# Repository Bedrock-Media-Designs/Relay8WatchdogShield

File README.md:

# Relay 8 Watchdog Shield for Relay Shield Carrier
Copyright 2019 Bedrock Media Productions Pty Ltd www.bedrockmediaproductions.com.au

EtherTen Shield for the SuperHouse Automation Relay Shield Carrier Board

Features:

watchdog Timer, Routed into Digital Pin 8
I2C Header for easy connection to the Relay Shield Carrier Board
More information:

Relay Carrier Shield <https://www.superhouse.tv/product/relay-shield-carrier-x4/>

Relay8 Watchdog Shield <https://bedrockmediaproductions.com.au/product/r8wds/>

 ## INSTALLATION
The design is saved as an EAGLE project. EAGLE PCB design software is available from www.cadsoftusa.com free for non-commercial use. To use this project download it and place the directory containing these files into the "eagle" directory on your computer. Then open EAGLE and navigate to the project.

 ## CREDITS
Designed by: 

Jonathan Oxer jon@oxer.com.au (Protoshort Layout for EtherTen)

James Kennewell james@bedrockmediaproductions.com.au (circuit design)

## DISTRIBUTION
The specific terms of distribution of this project are governed by the license referenced below.

## LICENSE
Licensed under the TAPR Open Hardware License (www.tapr.org/OHL). The "license" folder within this repository also contains a copy of this license in plain text format.

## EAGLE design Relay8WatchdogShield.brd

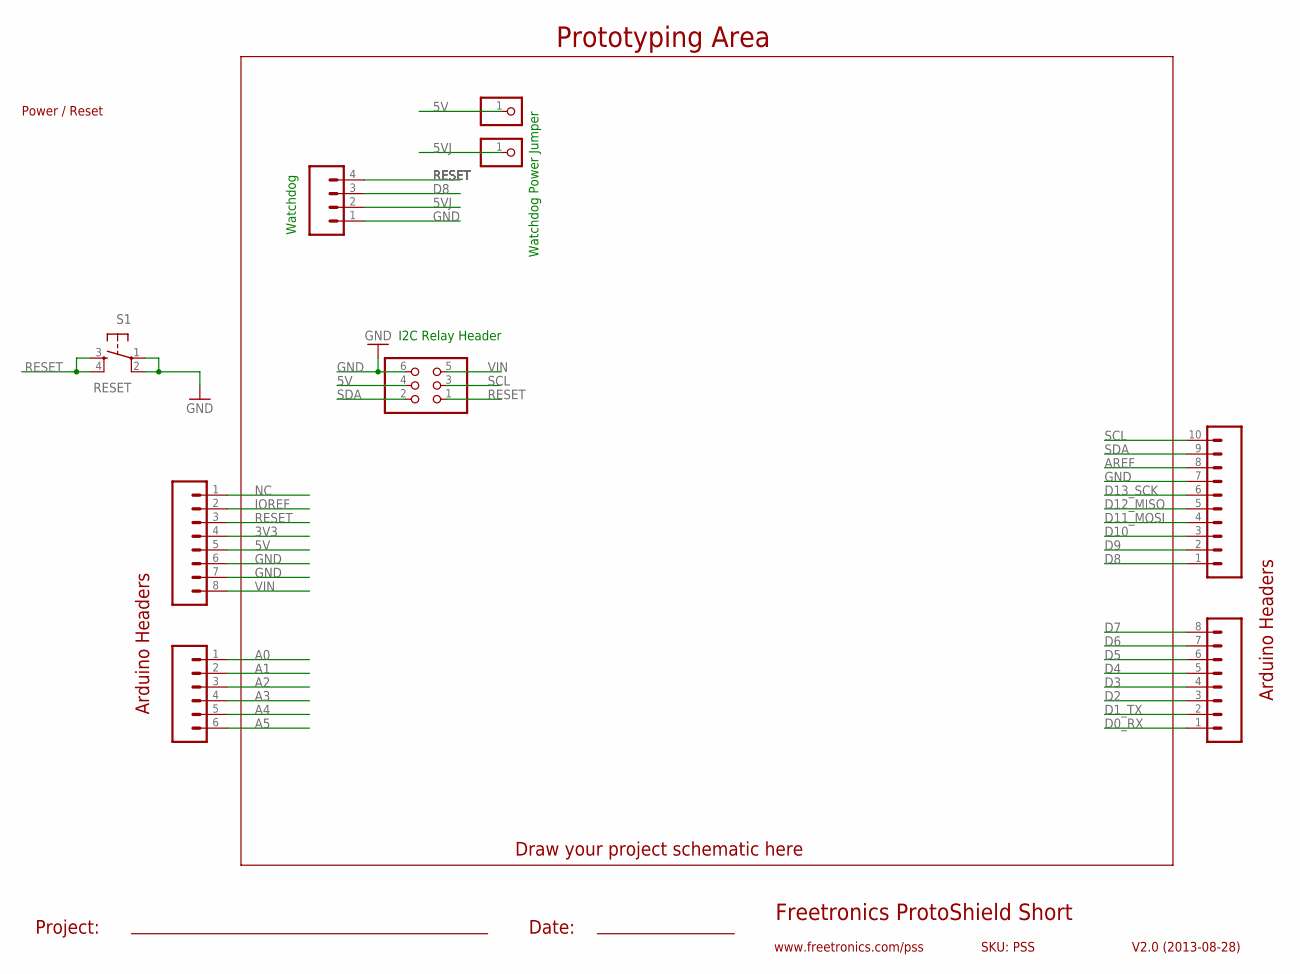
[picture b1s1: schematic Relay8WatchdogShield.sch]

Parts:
J1: Digital_0_7; 1X08
J2: Analog; 1X06
J3: Digital_8_13; 1X10
JP1, JP2: PINHD-1X1; 1X01
JP3: FREETRONICS-MASTER-V1_M04PTH; FREETRONICS-MASTER-V1_1X04
JP4: PINHD-2X3; 2X03
POWER: Power; 1X08
S1: RESET; TACTILE-PTH

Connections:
3V3: POWER.4
5V: JP1.1, JP4.4, POWER.5
5VJ: JP2.1, JP3.2
A0: J2.1
A1: J2.2
A2: J2.3
A3: J2.4
A4: J2.5
A5: J2.6
AREF: J3.8
D0_RX: J1.1
D1_TX: J1.2
D2: J1.3
D3: J1.4
D4: J1.5
D5: J1.6
D6: J1.7
D7: J1.8
D8: J3.1, JP3.3
D9: J3.2
D10: J3.3
D11_MOSI: J3.4
D12_MISO: J3.5
D13_SCK: J3.6
GND: J3.7, JP3.1, JP4.6, POWER.6, POWER.7, S1.1, S1.2
IOREF: POWER.2
NC: POWER.1
RESET: JP3.4, JP4.1, POWER.3, S1.3, S1.4
SCL: J3.10, JP4.3
SDA: J3.9, JP4.2
VIN: JP4.5, POWER.8

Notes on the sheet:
Freetronics ProtoShield Short
V2.0 (2013-08-28)
www.freetronics.com/pss
SKU: PSS
Prototyping Area
Arduino Headers
Power / Reset
Project:
Date:
Draw your project schematic here
Watchdog
I2C Relay Header
Watchdog Power Jumper

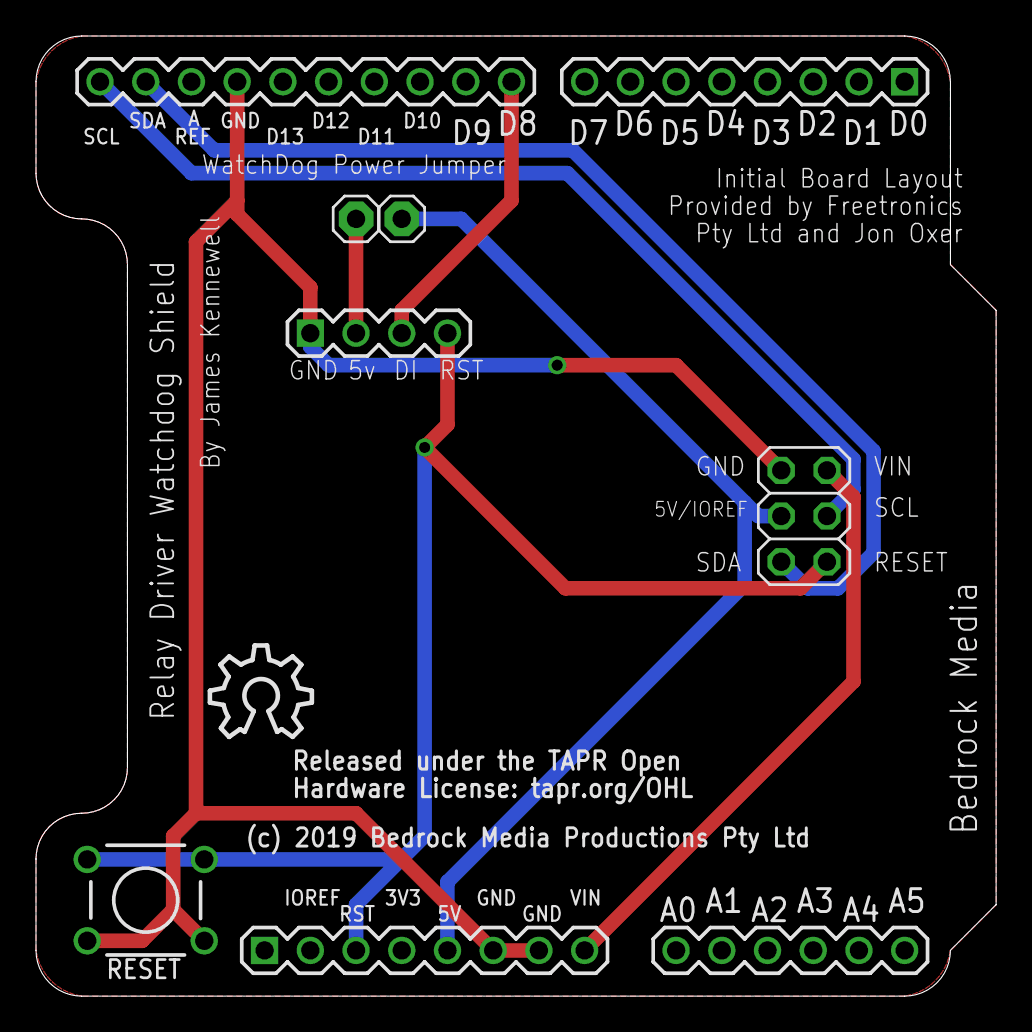
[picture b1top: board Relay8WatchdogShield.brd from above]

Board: 2 copper layers, 53.3 x 53.3 mm, 10 parts (0 on the bottom side), 8 nets.

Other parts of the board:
U$1: OSHW_10X200_NOTEXT

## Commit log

2019-09-07 Initial Upload
2019-09-18 Updated I2c Header
    Changed Header from 1x6 to 2x3 IDC Shrouded Header.

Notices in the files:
Relay8WatchdogShield.brd:
Hardware License: tapr.org/OHL
(c) 2019 Bedrock Media Productions Pty Ltd
